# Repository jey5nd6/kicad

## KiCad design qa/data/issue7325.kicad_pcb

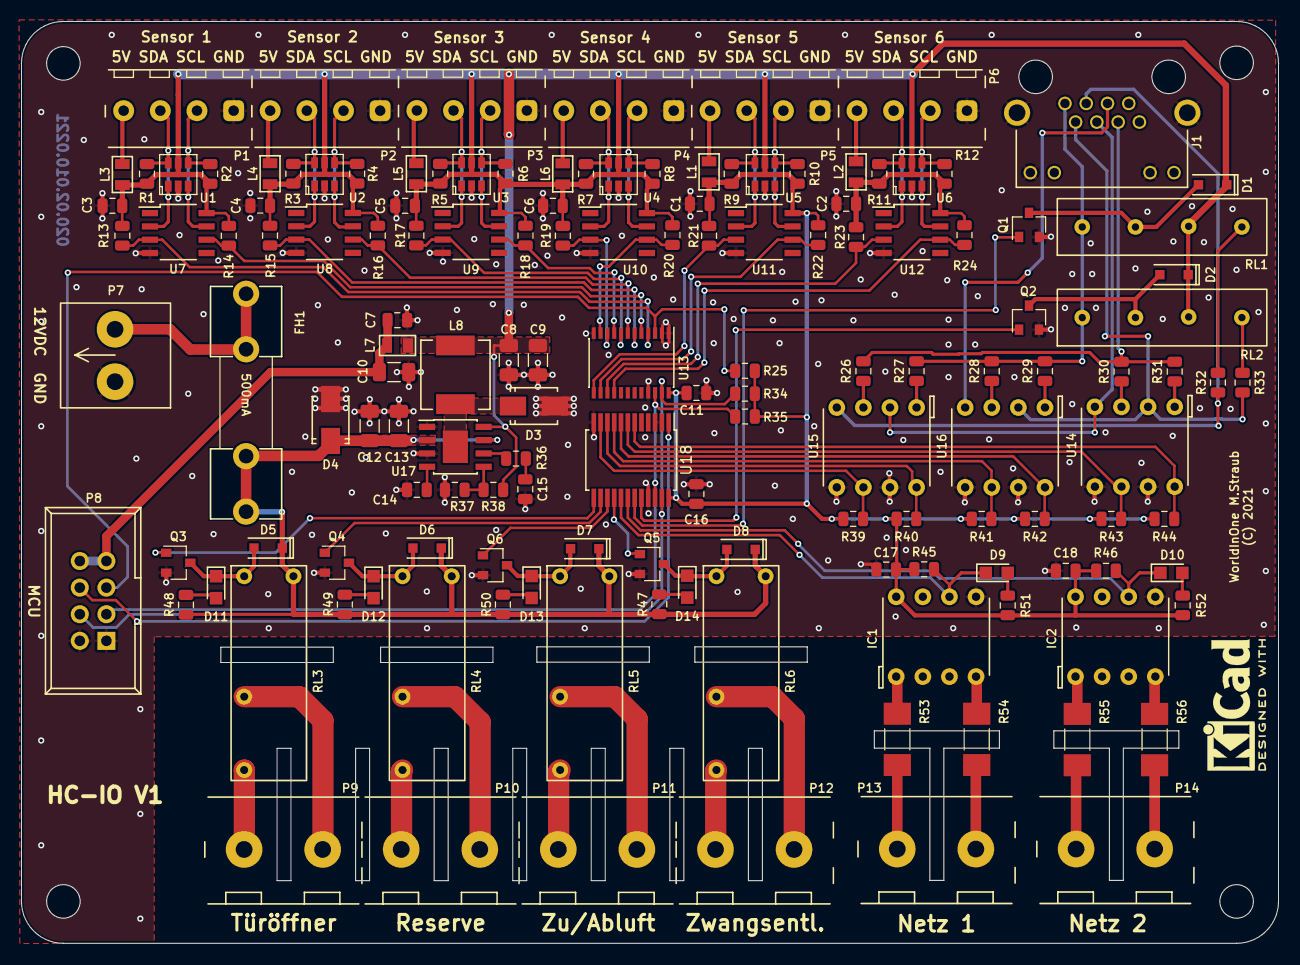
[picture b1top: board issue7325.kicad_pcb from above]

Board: 2 copper layers, 120.0 x 88.0 mm, 148 parts (0 on the bottom side), 100 nets.

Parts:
C1, C2, C3, C4, C5, C6: 1µ; C_0805_2012Metric_95
C7, C11, C14, C16, C17, C18: 100N; C_0805_2012Metric_60
C8, C9, C10, C12, C13: 22µ; C_1206_3216Metric_95
C15: 1.8N; C_0805_2012Metric_60
D1, D2, D5, D6, D7, D8: 1N4148WS; SOD-323
D3, D4: SS34; SMA_Standard
D9, D10: LED0805-Y; LED_0805
D11, D12, D13, D14: LED0805-G; LED_0805
FH1: FC5X20; Fuseholder5x20_horizontal_open_inline_1
IC1, IC2: HCPL-3760; DIP-8_W7.62mm_Socketed
J1: RJ45_LEDs_Shield
L1, L2, L3, L4, L5, L6, L7: FB; INDC2012X110
L8: 10µ; Inductor_0630
MH1, MH2, MH3, MH4: MHNP_M3; MountingHole_3.2mm_M3
P1, P2, P3, P4, P5, P6: KF128-4-3.5
P7: KF128-2-5.0
P8: IDCMV-4-2; IDC_Header_Straight_8pins
P9, P10, P11, P12, P13, P14: KF128-7.5-2; Terminal_Block_KF128_7.5mm-2pol
Q1, Q2, Q3, Q4, Q5, Q6: BSS138; SOT-23
R1, R2, R3, R4, R5, R6, R7, R8, R9, R10, R11, R12: 680E; R_0805_2012Metric
R13, R14, R15, R16, R17, R18, R19, R20, R21, R22, R23, R24, R25, R34, R35: 2.2K; R_0805_2012Metric
R26, R27, R28, R29, R30: 150E; R_0805_2012Metric
R31: 560E; R_0805_2012Metric
R32, R33: 10K; R_0805_2012Metric
R36: 27K; R_0805_2012Metric
R37: 9.53K; R_0805_2012Metric
R38: 49.9K; R_0805_2012Metric
R39, R40, R41, R42, R43, R44: 1K; R_0805_2012Metric
R45, R46, R51, R52: 4.7K; R_0805_2012Metric
R47, R48, R49, R50: 3.3K; R_0805_2012Metric
R53, R54, R55, R56: 82K; R_MELF_MMB-0207
RL1, RL2: SIP-1A5
RL3, RL4, RL5, RL6: G5NB-5; Relais_G5NB
U1, U2, U3, U4, U5, U6: USBLC6-2SC6; SOT-23-6
U7, U8, U9, U10, U11, U12: P82B715; SOIC-8_3.9x4.9mm_Pitch1.27mm
U13: PCA9548A; TSSOP-24_4.4x7.8mm_Pitch0.65mm
U14, U15, U16: LTV-827C; DIP-8_W7.62mm_Socketed
U17: AOZ3015; SOIC-8-1EP_3.9x4.9mm_Pitch1.27mm_PowerPAD
U18: PCF8575; SSOP-24_5.3x8.2mm_Pitch0.65mm

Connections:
/5V: C1.1, C2.1, C3.1, C4.1, C5.1, C6.1, C8.1, C9.1, C11.1, C16.2, C17.2, C18.2, D1.1 (K), D2.1 (K), IC1.8 (VCC), IC2.8 (VCC), L1.1, L2.1, L3.1, L4.1, L5.1, L6.1, L7.1, L8.2, R1.1, R2.2, R3.1, R4.2, R5.1, R6.2, R7.1, R8.2, R9.1, R10.2, R11.1, R12.2, R13.1, R14.1, R15.1, R16.1, R17.1, R18.1, R19.1, R20.1, R21.1, R22.1, R23.1, R24.1, R25.2, R34.1, R35.1, R38.2, R39.1, R40.1, R41.1, R42.1, R43.1, R44.1, R45.1, R46.1, R51.1, R52.1, RL1.3, RL2.3, U1.5 (VBUS), U2.5 (VBUS), U3.5 (VBUS), U4.5 (VBUS), U5.5 (VBUS), U6.5 (VBUS), U7.8 (Vcc), U8.8 (Vcc), U9.8 (Vcc), U10.8 (Vcc), U11.8 (Vcc), U12.8 (Vcc), U13.24 (VCC), U17.8 (VOUT), U18.24 (VDD)
/5VMCU: C7.1, C10.1, L7.2, P8.7, P8.8
/12V: C12.1, C13.1, D4.1 (K), D5.1 (K), D6.1 (K), D7.1 (K), D8.1 (K), FH1.2, R47.2, R48.2, R49.2, R50.2, RL3.4, RL4.4, RL5.4, RL6.4, U17.2 (VIN), U17.7 (EN)
/230V & general interface/230V1: D9.1 (K), IC1.6 (Vo), R45.2, U18.17 (IO1_4)
/230V & general interface/230V2: D10.1 (K), IC2.6 (Vo), R46.2, U18.18 (IO1_5)
/230V & general interface/AUX: Q4.1 (G), U18.14 (IO1_1)
/230V & general interface/BTL1: R42.2, U16.8, U18.8 (IO0_4)
/230V & general interface/BTL3: R40.2, U15.8, U18.10 (IO0_6)
/230V & general interface/BTL4: R41.2, U16.6, U18.9 (IO0_5)
/230V & general interface/BTL5: R44.2, U14.8, U18.6 (IO0_2)
/230V & general interface/BTL6: R39.2, U15.6, U18.11 (IO0_7)
/230V & general interface/BTL7: R43.2, U14.6, U18.7 (IO0_3)
/230V & general interface/BTP1: J1.1, R27.2, R28.2, R29.2, RL1.1, RL2.1
/230V & general interface/BTP2: J1.2, R33.2, U14.2, U16.2
/230V & general interface/BTP3: J1.3, R32.2, U15.4
/230V & general interface/BTP4: J1.4, U14.4, U15.2
/230V & general interface/BTP5: J1.5, U16.4
/230V & general interface/BTP6: J1.6, R26.2, R30.2, R31.2
/230V & general interface/DOOR: Q3.1 (G), U18.13 (IO1_0)
/230V & general interface/ENTFON: Q2.1 (G), U18.20 (IO1_7)
/230V & general interface/ENTFRH: Q1.1 (G), U18.19 (IO1_6)
/230V & general interface/ZUAB: Q6.1 (G), U18.15 (IO1_2)
/230V & general interface/ZWANG: Q5.1 (G), U18.16 (IO1_3)
/AM2315 sensors I2C interface/S0SCL: P1.2, R2.1, U1.3 (IO2), U1.4 (IO2), U7.7 (Ly)
/AM2315 sensors I2C interface/S0SDA: P1.3, R1.2, U1.1 (IO1), U1.6 (IO1), U7.2 (Lx)
/AM2315 sensors I2C interface/S1SCL: P2.2, R4.1, U2.3 (IO2), U2.4 (IO2), U8.7 (Ly)
/AM2315 sensors I2C interface/S1SDA: P2.3, R3.2, U2.1 (IO1), U2.6 (IO1), U8.2 (Lx)
/AM2315 sensors I2C interface/S2SCL: P3.2, R6.1, U3.3 (IO2), U3.4 (IO2), U9.7 (Ly)
/AM2315 sensors I2C interface/S2SDA: P3.3, R5.2, U3.1 (IO1), U3.6 (IO1), U9.2 (Lx)
/AM2315 sensors I2C interface/S3SCL: P4.2, R8.1, U4.3 (IO2), U4.4 (IO2), U10.7 (Ly)
/AM2315 sensors I2C interface/S3SDA: P4.3, R7.2, U4.1 (IO1), U4.6 (IO1), U10.2 (Lx)
/AM2315 sensors I2C interface/S4SCL: P5.2, R10.1, U5.3 (IO2), U5.4 (IO2), U11.7 (Ly)
/AM2315 sensors I2C interface/S4SDA: P5.3, R9.2, U5.1 (IO1), U5.6 (IO1), U11.2 (Lx)
/AM2315 sensors I2C interface/S5SCL: P6.2, R12.1, U6.3 (IO2), U6.4 (IO2), U12.7 (Ly)
/AM2315 sensors I2C interface/S5SDA: P6.3, R11.2, U6.1 (IO1), U6.6 (IO1), U12.2 (Lx)
/NIOINT: P8.6, U18.1 (~INT)
/NIORESET: P8.5, R25.1, U13.3 (~RESET)
/SCL: P8.3, R35.2, U13.22 (SCL), U18.22 (SCL)
/SDA: P8.4, R34.2, U13.23 (SDA), U18.23 (SDA)
GND: C1.2, C2.2, C3.2, C4.2, C5.2, C6.2, C7.2, C8.2, C9.2, C10.2, C11.2, C12.2, C13.2, C14.2, C15.2, C16.1, C17.1, C18.1, D3.2 (A), D4.2 (A), IC1.5 (GND), IC2.5 (GND), J1.GK, J1.Shld (Shield), J1.YK, P1.1, P2.1, P3.1, P4.1, P5.1, P6.1, P7.1, P8.1, P8.2, Q1.2 (S), Q2.2 (S), Q3.2 (S), Q4.2 (S), Q5.2 (S), Q6.2 (S), R37.1, U1.2 (GND), U2.2 (GND), U3.2 (GND), U4.2 (GND), U5.2 (GND), U6.2 (GND), U7.4 (GND), U8.4 (GND), U9.4 (GND), U10.4 (GND), U11.4 (GND), U12.4 (GND), U13.1 (A0), U13.2 (A1), U13.12 (GND), U13.21 (A2), U14.5, U14.7, U15.5, U15.7, U16.5, U16.7, U17.1 (PGND), U17.3 (AGND), U18.2 (A1), U18.3 (A2), U18.12 (VSS), U18.21 (A0)
unnamed: C14.1, U17.4 (VCC)
unnamed: C15.1, R36.1
unnamed: D1.2 (A), Q1.3 (D), RL1.2
unnamed: D2.2 (A), Q2.3 (D), RL2.2
unnamed: D3.1 (K), L8.1, U17.9 (LX)
unnamed: D9.2 (A), R51.2
unnamed: D10.2 (A), R52.2
unnamed: D5.2 (A), D11.1 (K), Q3.3 (D), RL3.1
unnamed: D11.2 (A), R48.1
unnamed: D6.2 (A), D12.1 (K), Q4.3 (D), RL4.1
unnamed: D12.2 (A), R49.1
unnamed: D7.2 (A), D13.1 (K), Q6.3 (D), RL5.1
unnamed: D13.2 (A), R50.1
unnamed: D8.2 (A), D14.1 (K), Q5.3 (D), RL6.1
unnamed: D14.2 (A), R47.1
unnamed: FH1.1, P7.2
unnamed: IC1.1 (AC+), R53.1
unnamed: IC1.4 (AC-), R54.1
unnamed: IC2.1 (AC+), R55.1
unnamed: IC2.4 (AC-), R56.1
unnamed: L1.2, P5.4
unnamed: L2.2, P6.4
unnamed: L3.2, P1.4
unnamed: L4.2, P2.4
unnamed: L5.2, P3.4
unnamed: L6.2, P4.4
unnamed: P9.1, RL3.2
unnamed: P9.2, RL3.3
unnamed: P10.1, RL4.2
unnamed: P10.2, RL4.3
unnamed: P11.1, RL5.2
unnamed: P11.2, RL5.3
unnamed: P12.1, RL6.2
unnamed: P12.2, RL6.3
unnamed: P13.1, R54.2
unnamed: P13.2, R53.2
unnamed: P14.1, R56.2
unnamed: P14.2, R55.2
unnamed: R13.2, U7.3 (Sx), U13.4 (SD0)
unnamed: R14.2, U7.6 (Sy), U13.5 (SC0)
unnamed: R15.2, U8.3 (Sx), U13.6 (SD1)
unnamed: R16.2, U8.6 (Sy), U13.7 (SC1)
unnamed: R17.2, U9.3 (Sx), U13.8 (SD2)
unnamed: R18.2, U9.6 (Sy), U13.9 (SC2)
unnamed: R19.2, U10.3 (Sx), U13.10 (SD3)
unnamed: R20.2, U10.6 (Sy), U13.11 (SC3)
unnamed: R21.2, U11.3 (Sx), U13.13 (SD4)
unnamed: R22.2, U11.6 (Sy), U13.14 (SC4)
unnamed: R23.2, U12.3 (Sx), U13.15 (SD5)
unnamed: R24.2, U12.6 (Sy), U13.16 (SC5)
unnamed: R26.1, U15.3
unnamed: R27.1, U15.1
unnamed: R28.1, U16.3
unnamed: R29.1, U16.1
unnamed: R30.1, U14.3
unnamed: R31.1, U14.1
unnamed: R32.1, RL1.4
unnamed: R33.1, RL2.4
unnamed: R36.2, U17.6 (CMP)
unnamed: R37.2, R38.1, U17.5 (FB)

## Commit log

2020-06-06 Don't use the accelerator table in the menubars
    It seems that the accelerator table causes issues with
    keyboard events on MSW.
    Fixes https://gitlab.com/kicad/code/kicad/issues/1941
2021-03-17 Use threading for loading symbol libraries
2021-07-13 Add Ignored Violations tab to DRC dialog.
    Fixes https://gitlab.com/kicad/code/kicad/issues/7726
2021-07-13 Radial dimensions.
    ADDED radial type dimensions.
    Fixes https://gitlab.com/kicad/code/kicad/issues/2056
2021-07-13 Add cross-probing between PCB (markers) and DRC marker list.
    Fixes https://gitlab.com/kicad/code/kicad/issues/7246
2021-07-13 Add DRC tests for text height and text thickness.
    Fixes https://gitlab.com/kicad/code/kicad/issues/8683
2021-07-13 Add footprint library checing to DRC.
    Fixes https://gitlab.com/kicad/code/kicad/issues/6821
2021-07-13 Add default violation severities for new violations.
2021-07-14 Push most of PCB_SHAPE impl down in to EDA_SHAPE.
2021-09-06 Overhaul arc internal model to not over-specify information.
2021-09-06 Replace individual LIB_* shapes with LIB_SHAPE (based on EDA_SHAPE).
    Also moves to more capable FILL_T model that can be shared.
2021-09-06 Shorter names before things get out of hand.
    Also, remove comments indicating CURVE is a Bezier. Just call it a
    BEZIER.
2021-09-06 Units cleanup.
2021-09-06 Cleanup.
2021-09-06 Prefer wxASSERT to assert.
    The former gives warning when not running under a debugger; the latter
    does not.
2021-09-06 User-configureable dash styles (and dash-dot-dot).
    ADDED: Schematic Setup properties for dash length and gap length.
    ADDED: dash-dot-dot line style
    Fixes https://gitlab.com/kicad/code/kicad/issues/2206
2021-09-06 Import Altium radial dimensions to KiCad radial dimensions.
    (We converted them to KiCad leaders in 6.0 because we didn't have
    radial dimensions yet.)
    Fixes https://gitlab.com/kicad/code/kicad/issues/8789
2021-09-06 Shapes for schematic.
    ADDED arc, circle and rectangle shapes for schematic. Shapes support
    line styles and fill colors.
    CHANGED sheet background color in Edit Text & Graphics Properties to
    fill color (and it now affects shapes).
    Pushed STROKE_PARAMS down into common and moved all shapes to using it
    for stroke descriptions.
2021-09-06 Map Altium bold dimension text to a greater text thickness.
2021-09-06 Use board maxError value, and return SH_ARC for unfilled circle.
2021-09-06 Hook up zone-pad connections to custom rules.
    ADDED zone_connection constraint.
    ADDED thermal_relief_gap and thermal_spoke_width constraints.
    ADDED angle override for thermal relief spokes in Pad Properties.
    Fixes https://gitlab.com/kicad/code/kicad/issues/4067
2021-09-06 Copper sliver checking.
    ADDED DRCE_COPPER_SLIVER DRC error.
    ADDED ADVANCED_CFG DRCSliverWidthTolerance and DRCSliverAngleTolerance.
    Fixes https://gitlab.com/kicad/code/kicad/issues/2183
2021-09-06 Starved thermals DRC checking.
    ADDED min_resolved_spokes constraint.
    ADDED "Thermal relief connection to zone incomplete" violation.
    Fixes https://gitlab.com/kicad/code/kicad/issues/2183
2021-09-06 Solder mask integrity testing.
    ADDED DRC test for solder mask aperture bridging copper from different
    nets.
    ADDED visualization of minimum web width processing for solder masks.
    ADDED allow_soldermask_bridges property for footprints.
    Fixes https://gitlab.com/kicad/code/kicad/issues/2183
    Fixes https://gitlab.com/kicad/code/kicad/issues/1792
2021-09-06 Mechanical clearance rules.
    ADDED mechanical_clearance and mechanical_hole_clearance constraints.
    Fixes https://gitlab.com/kicad/code/kicad/issues/2183
2021-09-06 Add mask-to-copper clearance parameter and rename mask margin.
2021-09-06 Add mechanical copper clearance testing for shapes.
    Also includes going from distance-based neighbor exclusion to angle-
    based. (Distance doesn't work when very short segments are followed
    by very long ones.)
    Fixes https://gitlab.com/kicad/code/kicad/issues/2512
2021-09-06 Line styles for PCBNew shapes.
    Fixes https://gitlab.com/kicad/code/kicad/issues/2150
2021-09-06 Add a checker for copper-to-copper clearance within a single zone.
    Fixes https://gitlab.com/kicad/code/kicad/issues/2512
2021-09-06 Support for dielectric colors in board stackup.
    Fixes https://gitlab.com/kicad/code/kicad/issues/8491
2021-09-06 Allow min/max/opt to come from different rules.
2021-09-06 Fix compiler warning.
    Note: we've never read these values so they no longer exist in the
    footprint data structures.
2021-09-06 Fix solder mask plotting issues.
    1) Don't plot all footprint texts for each footprint graphic item.
    2) Enforce min web thickness around board shapes and board text.
    3) Enforce min web thickness around footprint shapes
    4) Correctly handle multi-layer zones.
    (1) and (4) will get cherry-picked back to 6.0, so after rebasing
    won't actually appear in this changelist anymore....
2021-09-06 Formatting.
2021-09-06 Less flashing of the progress bar.
2021-09-06 Improve clearance and constraint resolution reporting.
    1) Report on all applicable clearance types
    2) Don't double-book constraints if they're used by more than one
    test provider
    Fixes https://gitlab.com/kicad/code/kicad/issues/8961
2021-09-06 Flatten a layer of indirection out of 3D config settings.
2021-09-06 Custom rule severities.
    ADDED severity token to custom rule syntax. Each rule can now define
    its own severity.
    Fixes https://gitlab.com/kicad/code/kicad/issues/6148
2021-09-06 When updating footprints indicate which were changed.
    Fixes https://gitlab.com/kicad/code/kicad/issues/4203
2021-09-06 All the preferences, all the time.
    Fixes https://gitlab.com/kicad/code/kicad/issues/7877
    Fixes https://gitlab.com/kicad/code/kicad/issues/5153
2021-09-06 ADDED exclude all violations of rule X.
    Fixes https://gitlab.com/kicad/code/kicad/issues/5463
2021-11-08 Rebuild view from scratch for python scripts.
    Fixes https://gitlab.com/kicad/code/kicad/issues/7065

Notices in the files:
qa/data/issue7325.kicad_pcb:
(C) 2021
